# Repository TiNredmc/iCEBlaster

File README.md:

# iCEBlaster

iCEBlaster. STM32 based iCE40 SPI bitstream loader tool with USB MSC Drag and Drop feature.

# Description

iCEBlaster is a Drag and Drop firmware loader via SPI for iCE40 FPGA. The brain of this project is based on STM32F042F6P6 Arm Cortex M0 microcontroller.

By using USB-FS library working as USB Mass storage device class (USB MSC) and with Virtual file system based on FAT12. Working together as USB Disk pre formatted with FAT12 file system with 512 Bytes per sector, 65535 total sectors, 4 sectors reserved for master boot record (sector 0) and File allocation tables(sector 1, 2 and 3). No longer use internal flash as medium storage. 
By copying the iCE40 FPGA Bitstream to the disk, 2 for loops in state machine inside STORAGE_Write_FS() receive data from USB buffer and send it over SPI in chucks of 512 bytes to FPGA. With this technique, no Internal flash is required. 

The iCE40's Bitstream loading sequence is something like this 
```
// Reset and enter SPI mode sequence.
1. Pull SPI CE Pin to Low
2. Pull CRESET Pin to Low
3. Wait for 2ms.
4. Release CRESET (to HIGH). At this point iCE40 is now in Slave SPI mode.
5. wait for 200ms to make sure iCE40's Configuration RAM (CRAM) is cleared.

// Bitstream loading sequence.
6. Sending Bitstream data via SPI bus (MSB first for each byte).
7. Send 12 dummy bytes (0x00).
8. (optional) Send 7 dummy bytes (0x00) and the SPI pin can be later reconfigure to use as normal PIO

// End of loading.
9. Release SPI CE Pin (to HIGH). The iCE40 will automagically start.
```

When done, The mcu release CRESET to let FPGA run the firmware that we just flash. Then perform the USB reconnect to have a new and ready to Drag and Drop USB Disk.

# Link(s)

[Hackaday.io](https://hackaday.io/project/185263-iceblaster)

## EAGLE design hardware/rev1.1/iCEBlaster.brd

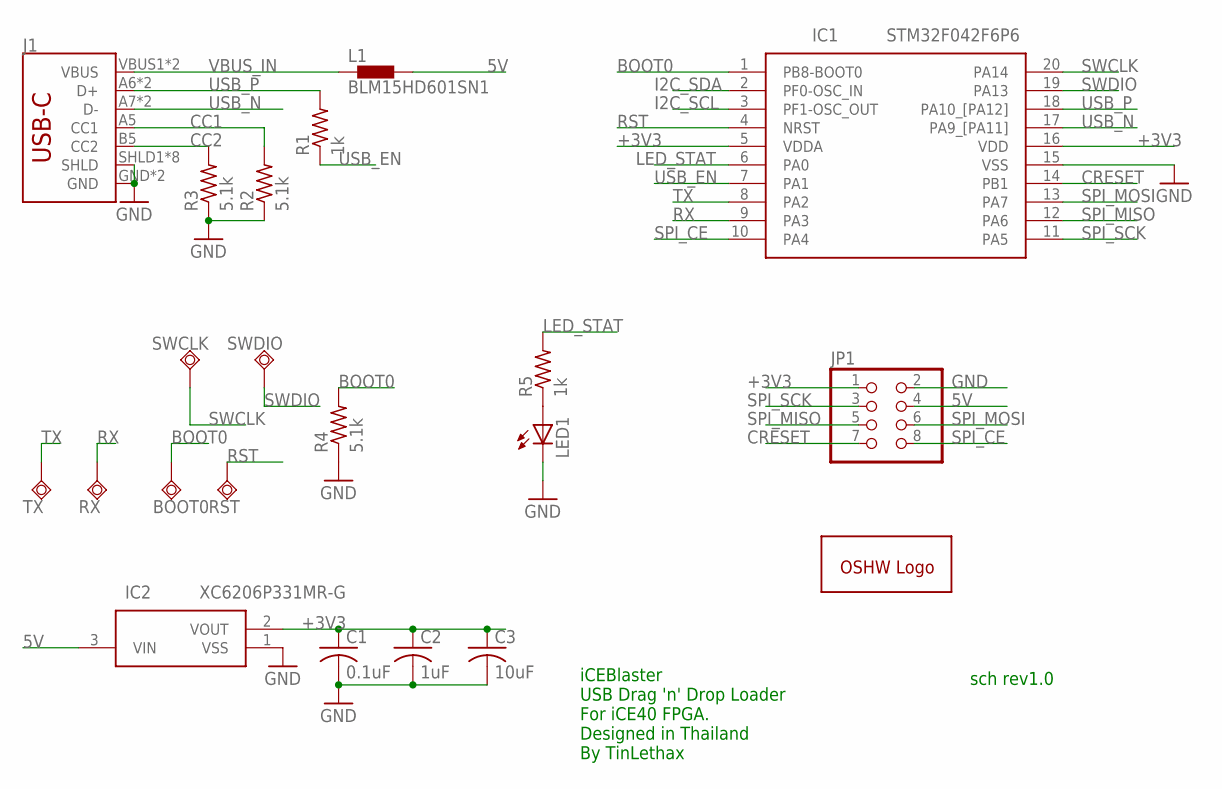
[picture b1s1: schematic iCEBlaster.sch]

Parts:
BOOT0: TPSQTP15SQ; TP15SQ
C1: 0.1uF; C0603
C2: 1uF; C0603
C3: 10uF; C0603
GOLD_ORB_SM1: OSHWLOGOLOGO5MM; OSHW_5MM
IC1: STM32F042F6P6; SOP65P640X120-20N
IC2: XC6206P331MR-G; SOT95P280X130-3N
J1: SPARKFUN-CONNECTORS_USB_C16PIN; SPARKFUN-CONNECTORS_USB-C-16P
JP1: PINHD-2X4/90; 2X04/90
L1: BLM15HD601SN1; 0402
LED1: LEDCHIP-LED0603; CHIP-LED0603
R1, R5: 1k; R0603
R2, R3, R4: 5.1k; R0603
RST: TPSQTP15SQ; TP15SQ
RX: TPSQTP15SQ; TP15SQ
SWCLK: TPSQTP15SQ; TP15SQ
SWDIO: TPSQTP15SQ; TP15SQ
TX: TPSQTP15SQ; TP15SQ

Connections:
5V: IC2.3 (VIN), JP1.4, L1.2
+3V3: C1.1, C2.1, C3.1, IC1.5 (VDDA), IC1.16 (VDD), IC2.2 (VOUT), JP1.1
BOOT0: BOOT0.TP, IC1.1 (PB8-BOOT0), R4.2
CC1: J1.A5 (CC1), R2.2
CC2: J1.B5 (CC2), R3.2
CRESET: IC1.14 (PB1), JP1.7
GND: C1.2, C2.2, C3.2, IC1.15 (VSS), IC2.1 (VSS), J1.GND, J1.GND2 (GND), J1.SHLD1 (SHLD), J1.SHLD2 (SHLD), J1.SHLD3 (SHLD), J1.SHLD4 (SHLD), J1.SHLD5 (SHLD), J1.SHLD6 (SHLD), J1.SHLD7 (SHLD), J1.SHLD8 (SHLD), JP1.2, LED1.C, R2.1, R3.1, R4.1
I2C_SCL: IC1.3 (PF1-OSC_OUT)
I2C_SDA: IC1.2 (PF0-OSC_IN)
LED: LED1.A, R5.1
LED_STAT: IC1.6 (PA0), R5.2
RST: IC1.4 (NRST), RST.TP
RX: IC1.9 (PA3), RX.TP
SPI_CE: IC1.10 (PA4), JP1.8
SPI_MISO: IC1.12 (PA6), JP1.5
SPI_MOSI: IC1.13 (PA7), JP1.6
SPI_SCK: IC1.11 (PA5), JP1.3
SWCLK: IC1.20 (PA14), SWCLK.TP
SWDIO: IC1.19 (PA13), SWDIO.TP
TX: IC1.8 (PA2), TX.TP
USB_EN: IC1.7 (PA1), R1.1
USB_N: IC1.17 (PA9_[PA11]), J1.A7 (D-), J1.B7 (D-)
USB_P: IC1.18 (PA10_[PA12]), J1.A6 (D+), J1.B6 (D+), R1.2
VBUS_IN: J1.VBUS1 (VBUS), J1.VBUS2 (VBUS), L1.1

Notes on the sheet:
iCEBlaster USB Drag 'n' Drop Loader For iCE40 FPGA. Designed in Thailand By TinLethax
sch rev1.0

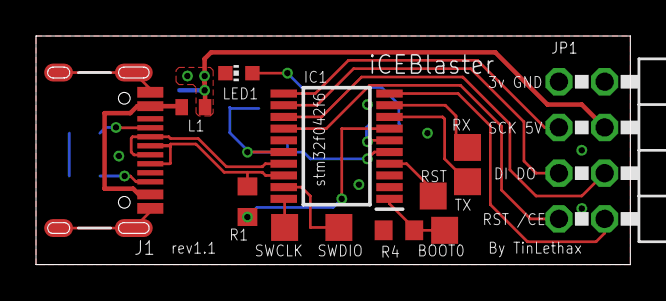
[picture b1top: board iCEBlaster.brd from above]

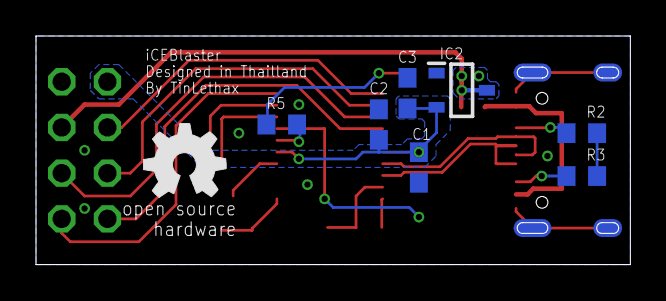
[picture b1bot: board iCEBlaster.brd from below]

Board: 2 copper layers, 33.0 x 12.7 mm, 21 parts (8 on the bottom side), 22 nets.

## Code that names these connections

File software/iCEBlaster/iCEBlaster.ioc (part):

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Mcu.Name=STM32F042F6Px
Mcu.Package=TSSOP20
Mcu.UserName=STM32F042F6Px
PA0.GPIOParameters=GPIO_Label
PA0.GPIO_Label=LED_STAT
PA0.Signal=GPIO_Output
PA1.GPIOParameters=PinState,GPIO_PuPd,GPIO_Label,GPIO_ModeDefaultOutputPP
PA1.GPIO_Label=USB_EN
PA1.GPIO_ModeDefaultOutputPP=GPIO_MODE_OUTPUT_OD
PA1.GPIO_PuPd=GPIO_NOPULL
PA1.PinState=GPIO_PIN_SET
PA1.Signal=GPIO_Output
PA11.Mode=Device
PA11.Signal=USB_DM
PA12.Mode=Device
PA12.Signal=USB_DP
PA13.Mode=Serial_Wire
PA13.Signal=SYS_SWDIO
PA14.Mode=Serial_Wire
PA14.Signal=SYS_SWCLK
PA4.GPIOParameters=GPIO_Label
PA4.GPIO_Label=SPI1_CE
PA4.Signal=GPIO_Output
PA5.Mode=Full_Duplex_Master
PA5.Signal=SPI1_SCK
PA6.Mode=Full_Duplex_Master
PA6.Signal=SPI1_MISO
PA7.Mode=Full_Duplex_Master
PA7.Signal=SPI1_MOSI
PB1.GPIOParameters=GPIO_Label
PB1.GPIO_Label=CRESET
PB1.Signal=GPIO_Output
RCC.SYSCLKFreq_VALUE=48000000
RCC.SYSCLKSource=RCC_SYSCLKSOURCE_HSI48
board=custom

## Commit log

2022-07-09 initial
2022-07-09 Create LICENSE
2022-07-10 Update FAT File system and code comments.
2022-07-12 Added rev1.1 PCB.
2022-09-01 Changed heap size to 0x400.
2022-09-01 iCEBlaster is now working!!
    - Tested with STM32F042F4P6.
    - Switch back to use switch case state machine instead of old crappy implementation that aim to
    save code space.
    - Changed block number to 510 to match with the File system.
    - Volume label is now working properly.
2022-09-05 I moved my project folder to my DevTLHX folder.
2022-09-05 Increased delay just a bit.
